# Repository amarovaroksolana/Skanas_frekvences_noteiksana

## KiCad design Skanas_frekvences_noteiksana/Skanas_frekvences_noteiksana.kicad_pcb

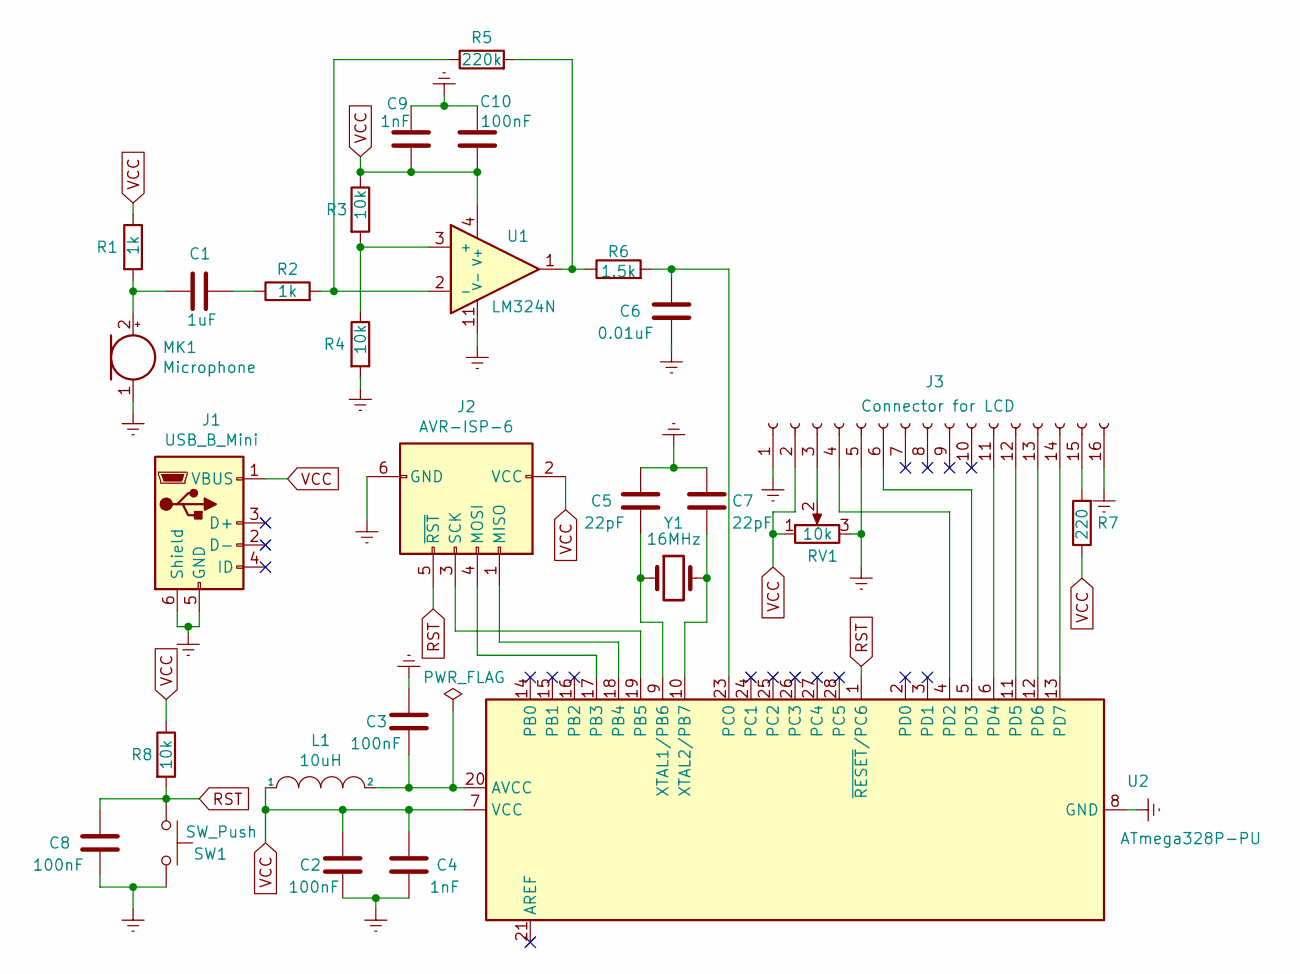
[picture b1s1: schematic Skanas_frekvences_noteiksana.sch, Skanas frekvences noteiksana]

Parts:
C1: 1uF; C_Disc_D3.8mm_W2.6mm_P2.50mm
C2, C3, C8, C10: 100nF; C_Disc_D3.8mm_W2.6mm_P2.50mm
C4, C9: 1nF; C_Disc_D3.8mm_W2.6mm_P2.50mm
C5, C7: 22pF; C_Disc_D3.8mm_W2.6mm_P2.50mm
C6: 0.01uF; C_Disc_D3.8mm_W2.6mm_P2.50mm
J1: USB_B_Mini; USB_Mini-B_Lumberg_2486_01_Horizontal
J2: AVR-ISP-6; IDC-Header_2x03_P2.54mm_Vertical
J3: Connector for LCD; PinSocket_1x16_P2.54mm_Vertical
L1: 10uH; L_Axial_L6.6mm_D2.7mm_P10.16mm_Horizontal_Vishay_IM-2
MK1: Microphone
R1, R2: 1k; R_Axial_DIN0207_L6.3mm_D2.5mm_P10.16mm_Horizontal
R3, R4, R8: 10k; R_Axial_DIN0207_L6.3mm_D2.5mm_P10.16mm_Horizontal
R5: 220k; R_Axial_DIN0207_L6.3mm_D2.5mm_P10.16mm_Horizontal
R6: 1.5k; R_Axial_DIN0207_L6.3mm_D2.5mm_P10.16mm_Horizontal
R7: 220; R_Axial_DIN0207_L6.3mm_D2.5mm_P10.16mm_Horizontal
RV1: 10k; Potentiometer_Runtron_RM-065_Vertical
SW1: SW_Push; SW_PUSH_6mm
U1: LM324N; DIP-14_W7.62mm
U2: ATmega328P-PU; DIP-28_W7.62mm
Y1: 16MHz; Crystal_HC18-U_Vertical

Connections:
Earth: C2.2, C3.1, C4.2, C5.1, C6.2, C7.1, C8.1, C9.2, C10.2, J1.5 (GND), J1.6 (Shield), J2.6 (GND), J3.1, J3.5, J3.16, MK1.1 (-), R4.2, RV1.3, SW1.2, U1.11 (V-), U2.8 (GND), U2.22 (GND)
unnamed: C1.1, R2.1
unnamed: C1.2, MK1.2 (+), R1.2
unnamed: C3.2, L1.2, U2.20 (AVCC)
unnamed: C5.2, U2.9 (XTAL1/PB6), Y1.1
unnamed: C6.1, R6.2, U2.23 (PC0)
unnamed: C7.2, U2.10 (XTAL2/PB7), Y1.2
unnamed: J2.1 (MISO), U2.18 (PB4)
unnamed: J2.3 (SCK), U2.19 (PB5)
unnamed: J2.4 (MOSI), U2.17 (PB3)
unnamed: J3.3, RV1.2
unnamed: J3.4, U2.4 (PD2)
unnamed: J3.6, U2.5 (PD3)
unnamed: J3.11, U2.6 (PD4)
unnamed: J3.12, U2.11 (PD5)
unnamed: J3.13, U2.12 (PD6)
unnamed: J3.14, U2.13 (PD7)
unnamed: J3.15, R7.2
unnamed: R2.2, R5.1, U1.2 (-)
unnamed: R3.2, R4.1, U1.3 (+)
unnamed: R5.2, R6.1, U1.1
RST: C8.2, J2.5 (~RST), R8.2, SW1.1, U2.1 (~RESET~/PC6)
VCC: C2.1, C4.1, C9.1, C10.1, J1.1 (VBUS), J2.2 (VCC), J3.2, L1.1, R1.1, R3.1, R7.1, R8.1, RV1.1, U1.4 (V+), U2.7 (VCC)

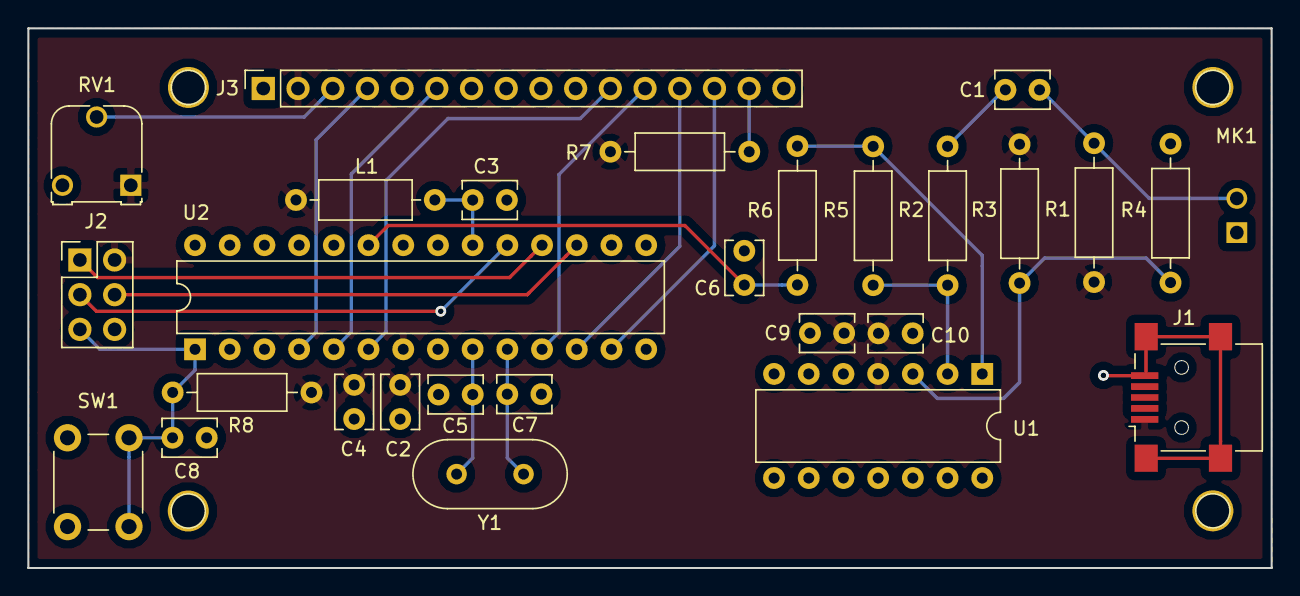
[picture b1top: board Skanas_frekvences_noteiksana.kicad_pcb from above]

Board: 2 copper layers, 91.0 x 39.5 mm, 28 parts (0 on the bottom side), 23 nets.

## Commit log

2019-04-28 Prakse
2019-06-12 Kursa_dabs
2019-06-13 Kursa_darbs
